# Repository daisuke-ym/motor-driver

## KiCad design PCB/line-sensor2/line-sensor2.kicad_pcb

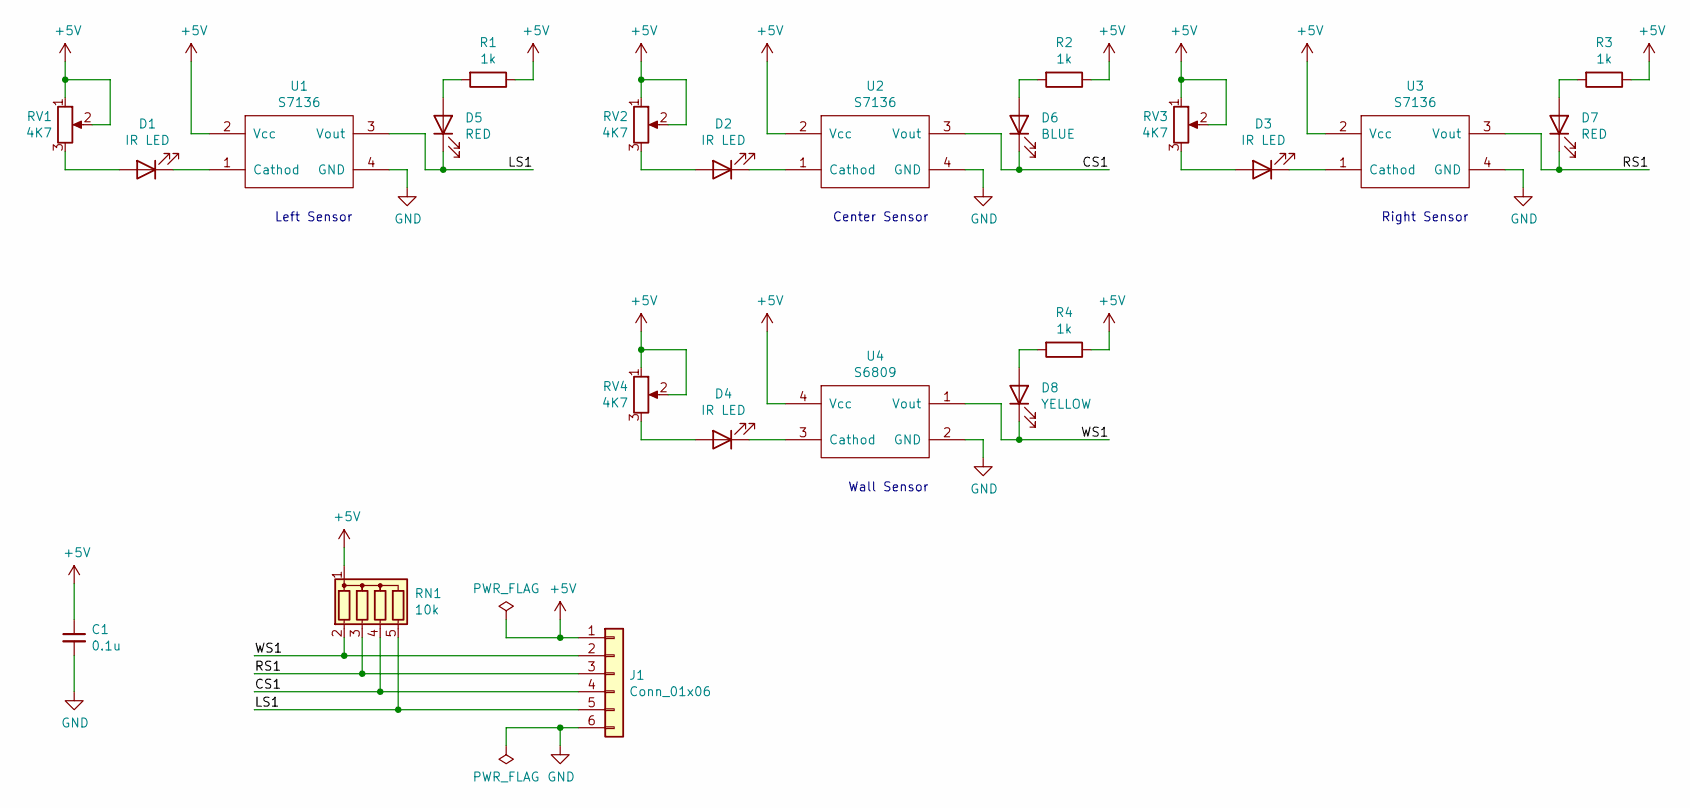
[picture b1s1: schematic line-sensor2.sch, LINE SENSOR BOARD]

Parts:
C1: 0.1u; C_Disc_D3.4mm_W2.1mm_P2.50mm
D1, D2, D3: IR LED; LED_D3.0mm_Clear
D4: IR LED; LED_D3.0mm_Horizontal_O3.81mm_Z6.0mm
D5, D7: RED; LED_D3.0mm_Clear
D6: BLUE; LED_D3.0mm_Clear
D8: YELLOW; LED_D3.0mm_Clear
J1: Conn_01x06; PinHeader_1x06_P2.54mm_Horizontal
R1, R2, R3, R4: 1k; R_Axial_DIN0207_L6.3mm_D2.5mm_P10.16mm_Horizontal
RN1: 10k; R_Array_SIP5
RV1, RV2, RV3, RV4: 4K7; GF063P1
U1, U2, U3: S7136
U4: S6809; S6809_Horizontal_Facedown

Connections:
+5V: C1.1, J1.1, R1.1, R2.1, R3.1, R4.1, RN1.1 (common), RV1.1, RV1.2, RV2.1, RV2.2, RV3.1, RV3.2, RV4.1, RV4.2, U1.2 (Vcc), U2.2 (Vcc), U3.2 (Vcc), U4.4 (Vcc)
/CS1: D6.1 (K), J1.4, RN1.4 (R3), U2.3 (Vout)
/LS1: D5.1 (K), J1.5, RN1.5 (R4), U1.3 (Vout)
/RS1: D7.1 (K), J1.3, RN1.3 (R2), U3.3 (Vout)
/WS1: D8.1 (K), J1.2, RN1.2 (R1), U4.1 (Vout)
GND: C1.2, J1.6, U1.4 (GND), U2.4 (GND), U3.4 (GND), U4.2 (GND)
unnamed: D1.1 (K), U1.1 (Cathod)
unnamed: D1.2 (A), RV1.3
unnamed: D2.1 (K), U2.1 (Cathod)
unnamed: D2.2 (A), RV2.3
unnamed: D3.1 (K), U3.1 (Cathod)
unnamed: D3.2 (A), RV3.3
unnamed: D4.1 (K), U4.3 (Cathod)
unnamed: D4.2 (A), RV4.3
unnamed: D5.2 (A), R1.2
unnamed: D6.2 (A), R2.2
unnamed: D7.2 (A), R3.2
unnamed: D8.2 (A), R4.2

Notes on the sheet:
Wall Sensor
Left Sensor
Center Sensor
Right Sensor

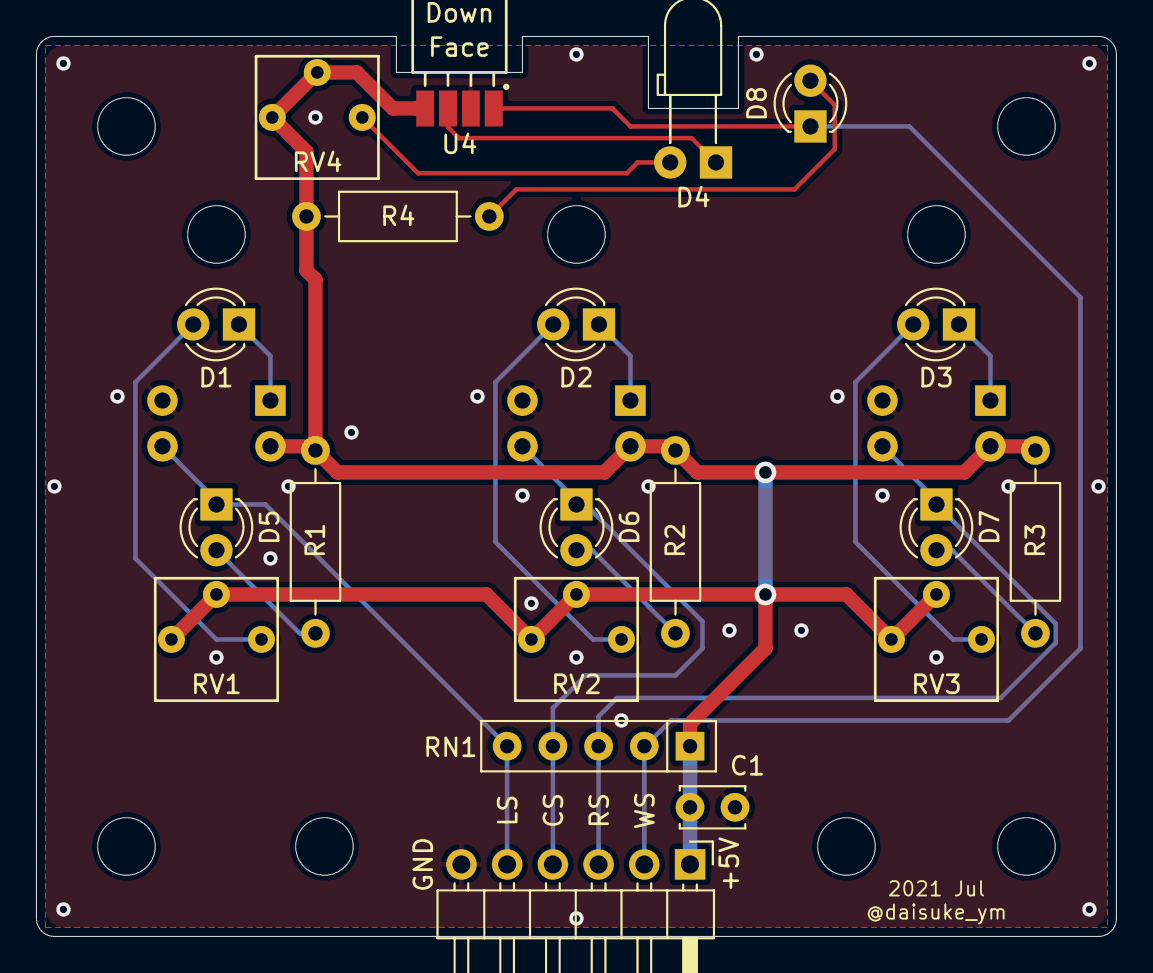
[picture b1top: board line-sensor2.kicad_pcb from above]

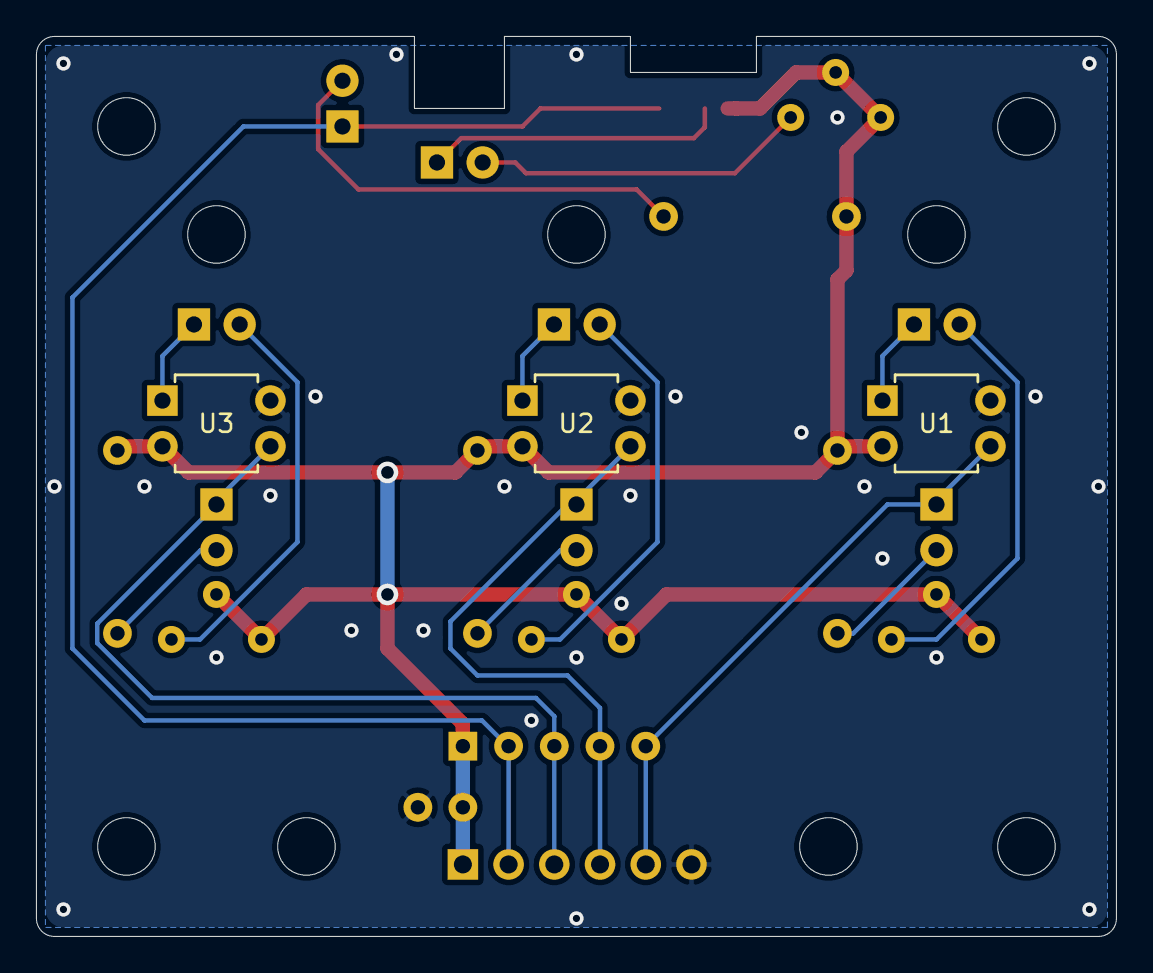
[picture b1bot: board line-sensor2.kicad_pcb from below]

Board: 2 copper layers, 60.0 x 50.0 mm, 32 parts (3 on the bottom side), 18 nets.

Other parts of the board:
MH1, MH2, MH3, MH4, MH5, MH6, MH8, MH9, MH10: MountingHole_3.2mm_M3

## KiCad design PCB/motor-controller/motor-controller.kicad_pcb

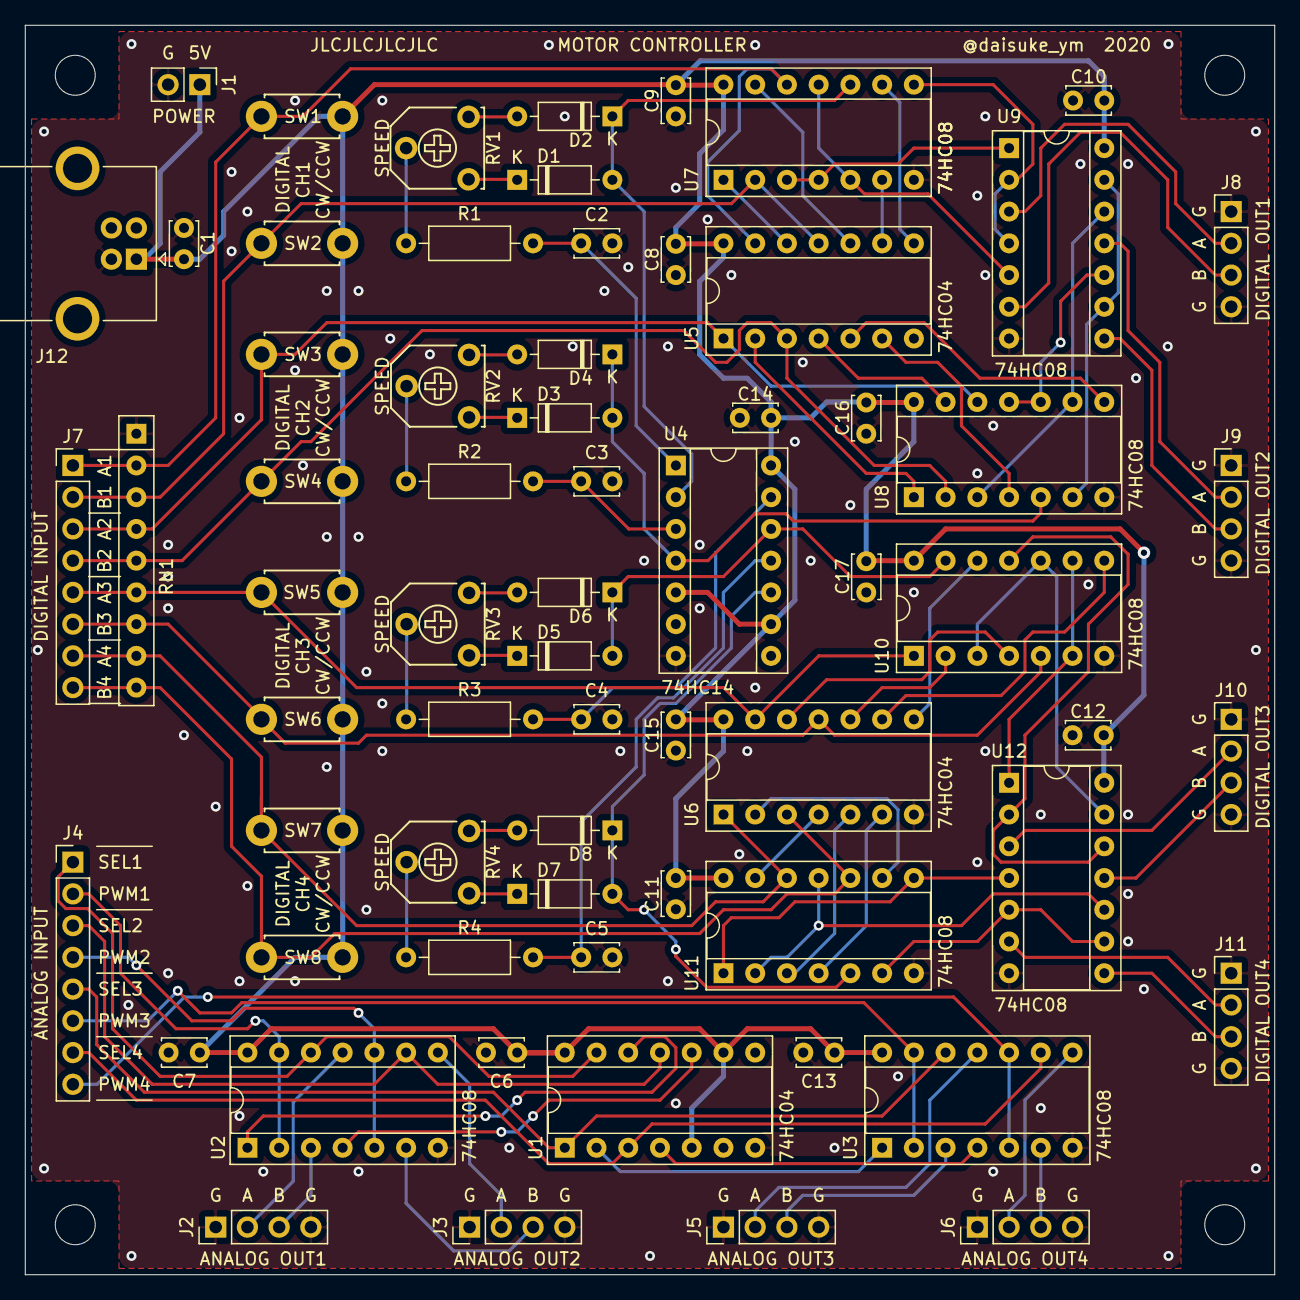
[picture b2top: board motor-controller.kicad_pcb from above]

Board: 2 copper layers, 100.0 x 100.0 mm, 70 parts (0 on the bottom side), 86 nets.

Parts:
C1, C2, C3, C4, C6, C7, C8, C9, C10, C11, C12, C13, C14, C15, C16, C17: 0.1u; C_Disc_D3.4mm_W2.1mm_P2.50mm
C5: C; C_Disc_D3.4mm_W2.1mm_P2.50mm
D1, D2, D3, D4, D5, D6, D7, D8: 1N4148; D_DO-35_SOD27_P7.62mm_Horizontal
J1: POWER; PinHeader_1x02_P2.54mm_Vertical
J2: ANALOG OUT1; PinHeader_1x04_P2.54mm_Vertical
J3: ANALOG OUT2; PinHeader_1x04_P2.54mm_Vertical
J4: ANALOG INPUT; PinHeader_1x08_P2.54mm_Vertical
J5: ANALOG OUT3; PinHeader_1x04_P2.54mm_Vertical
J6: ANALOG OUT4; PinHeader_1x04_P2.54mm_Vertical
J7: DIGITAL INPUT; PinHeader_1x08_P2.54mm_Vertical
J8: DIGITAL OUT1; PinHeader_1x04_P2.54mm_Vertical
J9: DIGITAL OUT2; PinHeader_1x04_P2.54mm_Vertical
J10: DIGITAL OUT3; PinHeader_1x04_P2.54mm_Vertical
J11: DIGITAL OUT4; PinHeader_1x04_P2.54mm_Vertical
J12: USB_B; USB_B_OST_USB-B1HSxx_Horizontal
MH1, MH2, MH3, MH4: MountingHole_3.2mm_M3
R1, R2, R3, R4: R; R_Axial_DIN0207_L6.3mm_D2.5mm_P10.16mm_Horizontal
RN1: 330; R_Array_SIP9
RV1, RV2, RV3, RV4: R_POT; TSR-065
SW1: D1A; TactSW_TVBP06_3.5x6.0-ThroughHole
SW2: D1B; TactSW_TVBP06_3.5x6.0-ThroughHole
SW3: D2A; TactSW_TVBP06_3.5x6.0-ThroughHole
SW4: D2B; TactSW_TVBP06_3.5x6.0-ThroughHole
SW5: D3A; TactSW_TVBP06_3.5x6.0-ThroughHole
SW6: D3B; TactSW_TVBP06_3.5x6.0-ThroughHole
SW7: D4A; TactSW_TVBP06_3.5x6.0-ThroughHole
SW8: D4B; TactSW_TVBP06_3.5x6.0-ThroughHole
U1, U5, U6: 74HC04; DIP-14_W7.62mm_Socket
U2, U3, U7, U8, U9, U10, U11, U12: 74HC08; DIP-14_W7.62mm_Socket
U4: 74HC14; DIP-14_W7.62mm_Socket

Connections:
+5V: C1.1, C6.1, C7.1, C8.1, C9.1, C10.1, C11.1, C12.1, C13.1, C14.1, C15.1, C16.1, C17.1, J1.1, J12.1, SW1.1, SW2.1, SW3.1, SW4.1, SW5.1, SW6.1, SW7.1, SW8.1, U1.5, U1.9, U1.14, U2.14, U3.14, U4.5, U4.9, U4.14, U5.14, U6.14, U7.14, U8.14, U9.14, U10.14, U11.14, U12.14
/AOUT1A: J2.2, U2.11
/AOUT1B: J2.3, U2.3
/AOUT2A: J3.2, U2.8
/AOUT2B: J3.3, U2.6
/AOUT3A: J5.2, U3.11
/AOUT3B: J5.3, U3.3
/AOUT4A: J6.2, U3.8
/AOUT4B: J6.3, U3.6
/DIN1A: J7.1, RN1.2, SW1.2, U5.13, U7.12
/DIN1B: J7.2, RN1.3, SW2.2, U5.11, U7.2
/DIN2A: J7.3, RN1.4, SW3.2, U5.1, U8.12
/DIN2B: J7.4, RN1.5, SW4.2, U5.3, U8.2
/DIN3A: J7.5, RN1.6, SW5.2, U6.13, U10.1
/DIN3B: J7.6, RN1.7, SW6.2, U6.11, U10.5
/DIN4A: J7.7, RN1.8, SW7.2, U6.1, U11.12
/DIN4B: J7.8, RN1.9, SW8.2, U6.3, U11.10
/DOUT1A: J8.2, U9.3
/DOUT1B: J8.3, U9.6
/DOUT2A: J9.2, U9.11
/DOUT2B: J9.3, U9.8
/DOUT3A: J10.2, U12.3
/DOUT3B: J10.3, U12.11
/DOUT4A: J11.2, U12.6
/DOUT4B: J11.3, U12.8
/OSC1: D1.2, D2.1, U4.2, U7.10
/OSC2: D3.2, D4.1, U4.4, U8.5
/OSC3: D5.2, D6.1, U4.12, U10.13
/OSC4: D7.2, D8.1, U4.10, U11.5
/PWM1IN: J4.2, U2.2, U2.13
/PWM2IN: J4.4, U2.5, U2.10
/PWM3IN: J4.6, U3.2, U3.13
/PWM4IN: J4.8, U3.5, U3.10
/SEL1: J4.1, U1.13, U2.12
/SEL2: J4.3, U1.11, U2.9
/SEL3: J4.5, U1.1, U3.12
/SEL4: J4.7, U1.3, U3.9
GND: C1.2, C2.2, C3.2, C4.2, C5.2, C6.2, C7.2, C8.2, C9.2, C10.2, C11.2, C12.2, C13.2, C14.2, C15.2, C16.2, C17.2, J1.2, J2.1, J2.4, J3.1, J3.4, J5.1, J5.4, J6.1, J6.4, J8.1, J8.4, J9.1, J9.4, J10.1, J10.4, J11.1, J11.4, J12.4, RN1.1, U1.7, U2.7, U3.7, U4.7, U5.7, U6.7, U7.7, U8.7, U9.7, U10.7, U11.7, U12.7
unnamed: C2.1, R1.2, U4.1
unnamed: C3.1, R2.2, U4.3
unnamed: C4.1, R3.2, U4.13
unnamed: C5.1, R4.2, U4.11
unnamed: D1.1, RV1.1
unnamed: D2.2, RV1.3
unnamed: D3.1, RV2.1
unnamed: D4.2, RV2.3
unnamed: D5.1, RV3.1
unnamed: D6.2, RV3.3
unnamed: D7.1, RV4.1
unnamed: D8.2, RV4.3
unnamed: R1.1, RV1.2
unnamed: R2.1, RV2.2
unnamed: R3.1, RV3.2
unnamed: R4.1, RV4.2
unnamed: U1.2, U3.1
unnamed: U1.4, U3.4
unnamed: U1.10, U2.4
unnamed: U1.12, U2.1
unnamed: U5.2, U8.1
unnamed: U5.4, U8.13
unnamed: U5.5, U8.8
unnamed: U5.6, U8.4
unnamed: U5.8, U7.9
unnamed: U5.9, U7.6
unnamed: U5.10, U7.13
unnamed: U5.12, U7.1
unnamed: U7.3, U7.4, U9.1
unnamed: U7.8, U9.2, U9.4
unnamed: U7.5, U7.11, U9.5
unnamed: U8.3, U8.9, U9.12
unnamed: U8.6, U9.9, U9.13
unnamed: U8.10, U8.11, U9.10
unnamed: U6.10, U10.2
unnamed: U6.12, U10.4
unnamed: U10.6, U10.9, U12.1
unnamed: U6.9, U10.8
unnamed: U10.3, U10.10, U12.13
unnamed: U10.11, U12.2, U12.12
unnamed: U6.8, U10.12
unnamed: U11.1, U11.8, U12.4
unnamed: U6.5, U11.3
unnamed: U6.6, U11.4
unnamed: U11.6, U12.5, U12.9
unnamed: U6.2, U11.9
unnamed: U11.2, U11.11, U12.10
unnamed: U6.4, U11.13

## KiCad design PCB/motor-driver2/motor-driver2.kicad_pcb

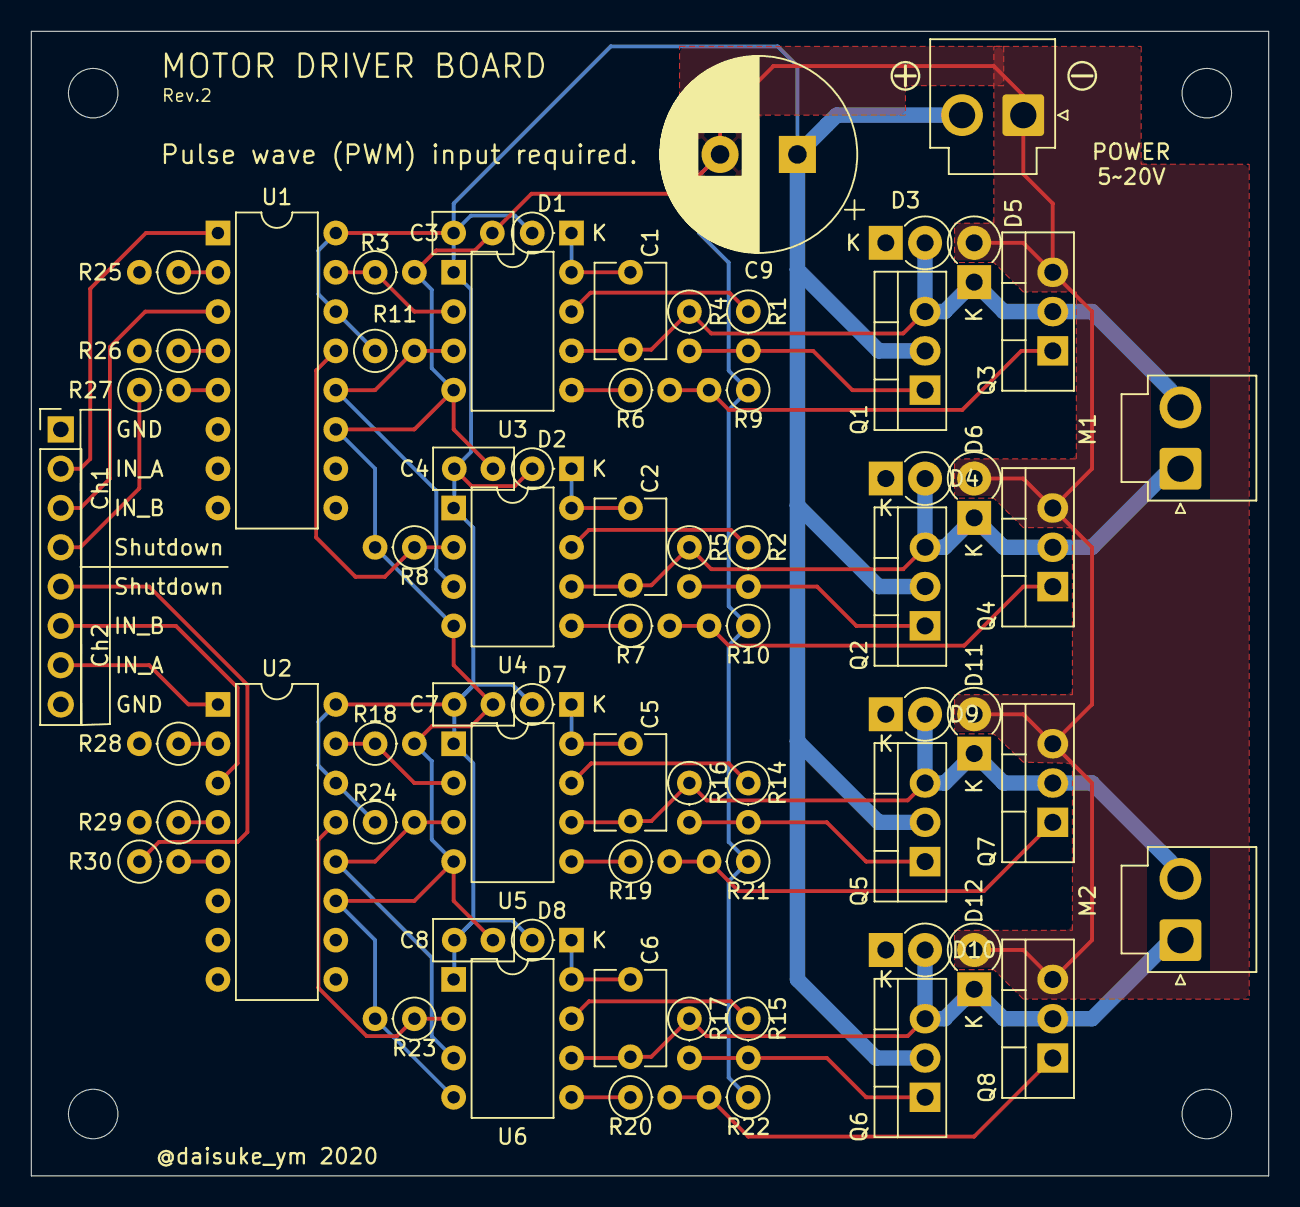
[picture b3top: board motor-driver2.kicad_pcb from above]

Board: 2 copper layers, 80.0 x 74.0 mm, 71 parts (0 on the bottom side), 45 nets.

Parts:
C1, C2, C5, C6: 10u; C_Disc_D6.0mm_W4.4mm_P5.00mm
C3, C4, C7, C8: 0.1u; C_Disc_D5.0mm_W2.5mm_P2.50mm
C9: 470u 50V; CP_Radial_D12.5mm_P5.00mm
D1, D2, D7, D8: 1N4148; D_DO-35_SOD27_P2.54mm_Vertical_KathodeUp
D3, D4, D5, D6, D9, D10, D11, D12: 1N4007; D_DO-41_SOD81_P2.54mm_Vertical_KathodeUp
J1: Motor Power; JST_VH_B2P-VH_1x02_P3.96mm_Vertical
J2: Input Logic; PinHeader_1x08_P2.54mm_Vertical
M1, M2: Motor_DC; JST_VH_B2P-VH_1x02_P3.96mm_Vertical
MH1, MH2, MH3, MH4: MountingHole_3.2mm_M3
Q1, Q2, Q3, Q4, Q5, Q6, Q7, Q8: Q_NMOS_GDS; TO-220-3_Vertical
R1, R2, R4, R5, R6, R7, R9, R10, R14, R15, R16, R17, R19, R20, R21, R22: 47k; R_Axial_DIN0207_L6.3mm_D2.5mm_P2.54mm_Vertical
R3, R8, R11, R18, R23, R24: 10k; R_Axial_DIN0207_L6.3mm_D2.5mm_P2.54mm_Vertical
R25, R26, R27, R28, R29, R30: 390; R_Axial_DIN0207_L6.3mm_D2.5mm_P2.54mm_Vertical
U1, U2: TLP627-4; DIP-16_W7.62mm
U3, U4, U5, U6: IR2302; DIP-8_W7.62mm

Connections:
+BATT: C3.1, C4.1, C7.1, C8.1, C9.1, D1.2, D2.2, D3.1, D4.1, D7.2, D8.2, D9.1, D10.1, J1.2, Q1.2, Q2.2, Q5.2, Q6.2, R11.1, R24.1, U1.14, U1.16, U2.14, U2.16, U3.1, U4.1, U5.1, U6.1
/DR_IN_A1: R3.1, U1.15, U3.2
/DR_IN_A2: R18.1, U2.15, U5.2
/DR_IN_B1: R8.1, U1.13, U4.2
/DR_IN_B2: R23.1, U2.13, U6.2
/DR_SD1: R11.2, U1.12, U3.3, U4.3
/DR_SD2: R24.2, U2.12, U5.3, U6.3
/IN_A1: J2.2, U1.1
/IN_A2: J2.7, U2.1
/IN_B1: J2.3, U1.3
/IN_B2: J2.6, U2.3
/IN_SD1: J2.4, R27.1
/IN_SD2: J2.5, R30.1
GND: J2.1, J2.8, R25.2, R26.2, R28.2, R29.2, U1.6, U2.6
GNDPWR: C3.2, C4.2, C7.2, C8.2, C9.2, D5.2, D6.2, D11.2, D12.2, J1.1, Q3.3, Q4.3, Q7.3, Q8.3, R3.2, R8.2, R9.1, R10.1, R18.2, R21.1, R22.1, R23.2, U1.11, U2.11, U3.4, U4.4, U5.4, U6.4
unnamed: C1.1, D1.1, U3.8
unnamed: C1.2, D3.2, D5.1, M1.2, Q1.3, Q3.2, R4.1, U3.6
unnamed: C2.1, D2.1, U4.8
unnamed: C2.2, D4.2, D6.1, M1.1, Q2.3, Q4.2, R5.1, U4.6
unnamed: C5.1, D7.1, U5.8
unnamed: C5.2, D9.2, D11.1, M2.2, Q5.3, Q7.2, R16.1, U5.6
unnamed: C6.1, D8.1, U6.8
unnamed: C6.2, D10.2, D12.1, M2.1, Q6.3, Q8.2, R17.1, U6.6
unnamed: Q1.1, R1.2, R4.2
unnamed: Q2.1, R2.2, R5.2
unnamed: Q3.1, R6.2, R9.2
unnamed: Q4.1, R7.2, R10.2
unnamed: Q5.1, R14.2, R16.2
unnamed: Q6.1, R15.2, R17.2
unnamed: Q7.1, R19.2, R21.2
unnamed: Q8.1, R20.2, R22.2
unnamed: R1.1, U3.7
unnamed: R2.1, U4.7
unnamed: R6.1, U3.5
unnamed: R7.1, U4.5
unnamed: R14.1, U5.7
unnamed: R15.1, U6.7
unnamed: R19.1, U5.5
unnamed: R20.1, U6.5
unnamed: R25.1, U1.2
unnamed: R26.1, U1.4
unnamed: R27.2, U1.5
unnamed: R28.1, U2.2
unnamed: R29.1, U2.4
unnamed: R30.2, U2.5

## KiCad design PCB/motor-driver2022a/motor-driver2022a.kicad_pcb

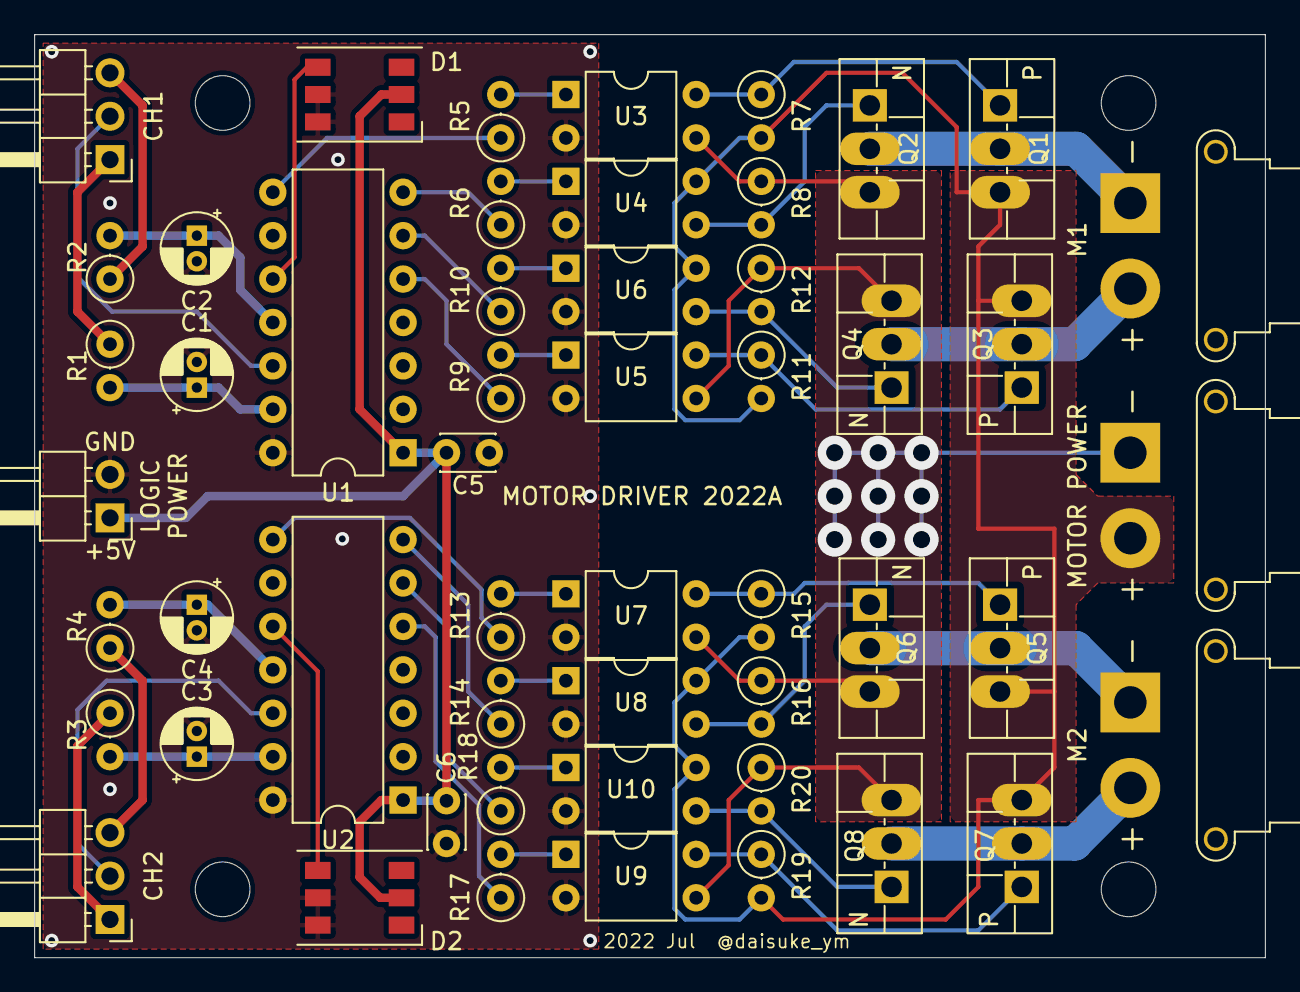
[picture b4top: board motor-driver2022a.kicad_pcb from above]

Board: 2 copper layers, 72.0 x 54.0 mm, 52 parts (0 on the bottom side), 44 nets.

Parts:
C1, C2, C3, C4: 10u; CP_Radial_D4.0mm_P1.50mm
C5, C6: 0.1u; C_Disc_D3.0mm_W2.0mm_P2.50mm
D1, D2: WS2813; LED_WS2812_PLCC6_5.0x5.0mm_P1.6mm
J1: Motor Power; AMASS_XT30PW-F_1x02_P2.50mm_Horizontal
J2: Logic Power; PinHeader_1x02_P2.54mm_Horizontal
J3: Ch1 Input; PinHeader_1x03_P2.54mm_Horizontal
J4: Ch2 Input; PinHeader_1x03_P2.54mm_Horizontal
M1, M2: Motor_DC; AMASS_XT30PW-F_1x02_P2.50mm_Horizontal
Q1, Q3, Q5, Q7: Q_PMOS_GDS; TO-220F-3_Vertical
Q2, Q4, Q6, Q8: Q_NMOS_GDS; TO-220F-3_Vertical
R1, R2, R3, R4: 4k7; R_Axial_DIN0207_L6.3mm_D2.5mm_P2.54mm_Vertical
R5, R6, R9, R10, R13, R14, R17, R18: 330; R_Axial_DIN0207_L6.3mm_D2.5mm_P2.54mm_Vertical
R7, R8, R11, R12, R15, R16, R19, R20: 2k2; R_Axial_DIN0207_L6.3mm_D2.5mm_P2.54mm_Vertical
U1, U2: ATtiny84-20PU; DIP-14_W7.62mm
U3, U4, U5, U6, U7, U8, U9, U10: TLP785; DIP-4_W7.62mm

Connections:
+5V: C5.1, C6.1, D1.2, D2.2, J2.1, U1.1, U2.1
+BATT: J1.2, Q1.3, Q3.3, Q5.3, Q7.3, R7.2, R11.2, R15.2, R19.2, U4.4, U6.4, U8.4, U10.4
/IN1A: J3.1, R1.1
/IN1AA: C1.1, R1.2, U1.13
/IN1B: J3.3, R2.1
/IN1BA: C2.1, R2.2, U1.11
/IN1M: J3.2, U1.12
/IN2A: J4.1, R3.1
/IN2AA: C3.1, R3.2, U2.13
/IN2B: J4.3, R4.1
/IN2BA: C4.1, R4.2, U2.11
/IN2M: J4.2, U2.12
/LED1: D1.4, U1.10
/LED2: D2.4, U2.10
/PC1A: R9.1, U1.5
/PC1B: R10.1, U1.6
/PC1C: R6.1, U1.7
/PC1D: R5.1, U1.8
/PC2A: R17.1, U2.5
/PC2B: R18.1, U2.6
/PC2C: R14.1, U2.7
/PC2D: R13.1, U2.8
GND: C1.2, C2.2, C3.2, C4.2, C5.2, C6.2, D1.5, D1.6, D2.5, D2.6, J2.2, U1.14, U2.14, U3.2, U4.2, U5.2, U6.2, U7.2, U8.2, U9.2, U10.2
GNDPWR: J1.1, Q2.3, Q4.3, Q6.3, Q8.3, R8.1, R12.1, R16.1, R20.1, U3.3, U5.3, U7.3, U9.3
unnamed: M1.1, Q1.2, Q2.2
unnamed: M1.2, Q3.2, Q4.2
unnamed: M2.1, Q5.2, Q6.2
unnamed: M2.2, Q7.2, Q8.2
unnamed: Q1.1, R7.1, U3.4
unnamed: Q2.1, R8.2, U4.3
unnamed: Q3.1, R11.1, U5.4
unnamed: Q4.1, R12.2, U6.3
unnamed: Q5.1, R15.1, U7.4
unnamed: Q6.1, R16.2, U8.3
unnamed: Q7.1, R19.1, U9.4
unnamed: Q8.1, R20.2, U10.3
unnamed: R5.2, U3.1
unnamed: R6.2, U4.1
unnamed: R9.2, U5.1
unnamed: R10.2, U6.1
unnamed: R13.2, U7.1
unnamed: R14.2, U8.1
unnamed: R17.2, U9.1
unnamed: R18.2, U10.1

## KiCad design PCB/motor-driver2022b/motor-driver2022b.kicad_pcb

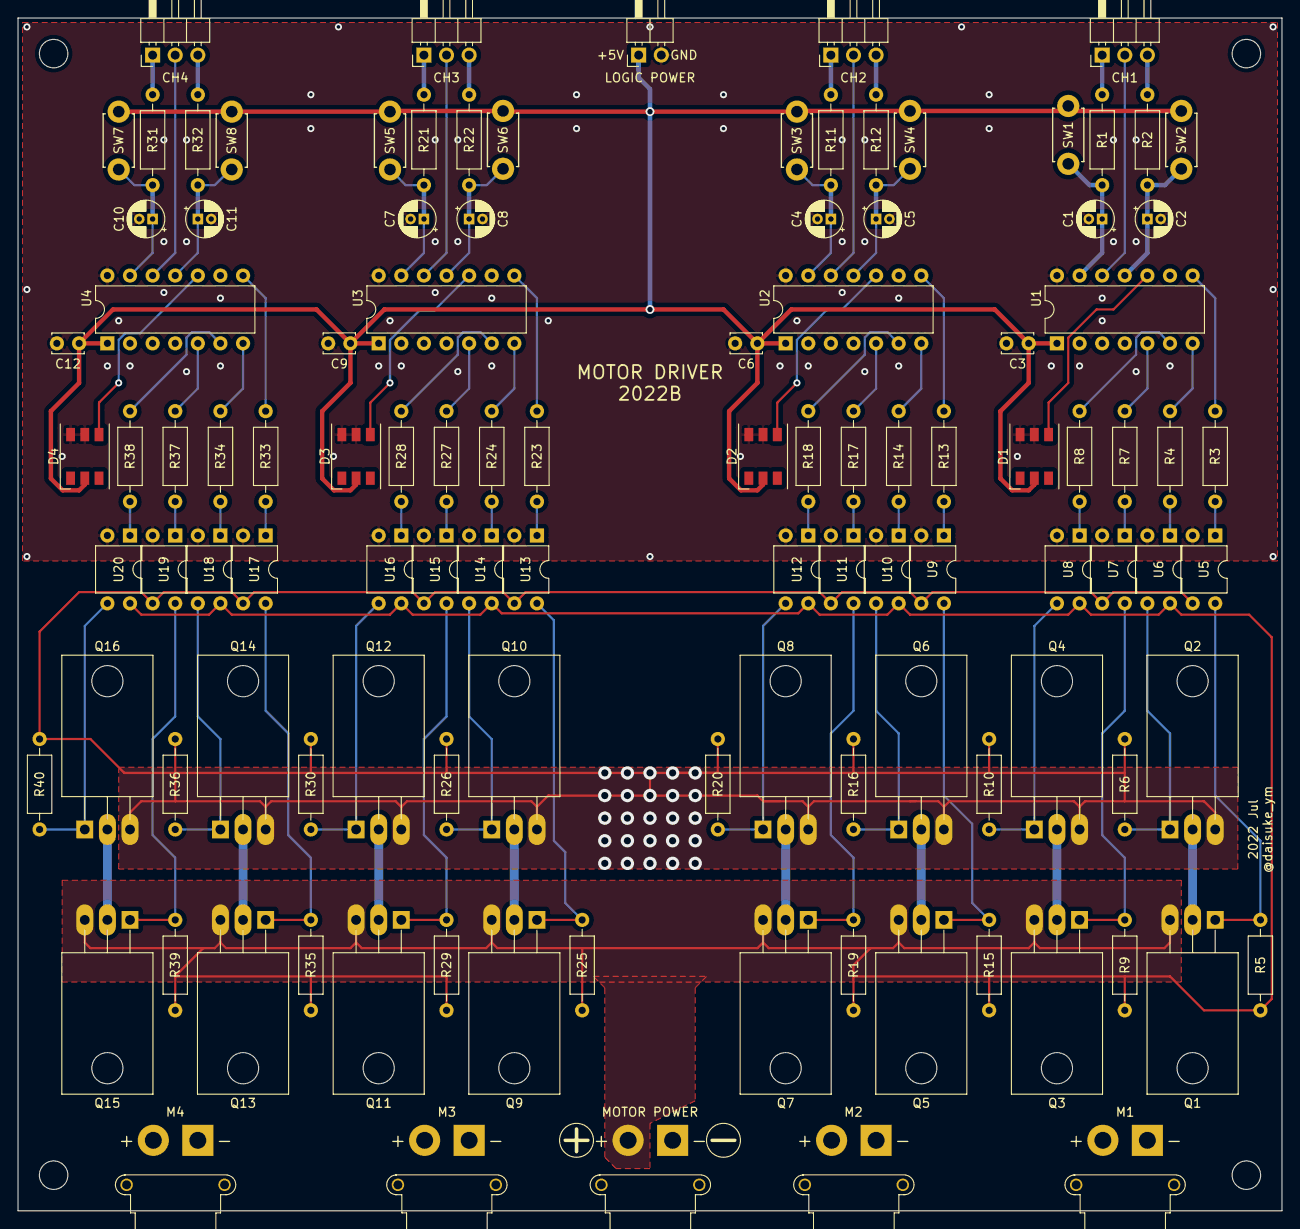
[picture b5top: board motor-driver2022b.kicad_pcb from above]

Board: 2 copper layers, 142.0 x 134.0 mm, 114 parts (0 on the bottom side), 84 nets.

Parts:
C1, C2, C4, C5, C7, C8, C10, C11: 10u; CP_Radial_D4.0mm_P1.50mm
C3, C6, C9, C12: 0.1u; C_Disc_D3.4mm_W2.1mm_P2.50mm
D1, D2, D3, D4: WS2813; LED_WS2812_PLCC6_5.0x5.0mm_P1.6mm
J1: Motor Power; AMASS_XT30PW-F_1x02_P2.50mm_Horizontal
J2: Logic Power; PinHeader_1x02_P2.54mm_Horizontal
J3: Input Ch1; PinHeader_1x03_P2.54mm_Horizontal
J4: Input Ch2; PinHeader_1x03_P2.54mm_Horizontal
J5: Input Ch3; PinHeader_1x03_P2.54mm_Horizontal
J6: Input Ch4; PinHeader_1x03_P2.54mm_Horizontal
M1, M2, M3, M4: Motor_DC; AMASS_XT30PW-F_1x02_P2.50mm_Horizontal
MH1, MH2, MH3, MH4: MountingHole_3.2mm_M3
Q1, Q3, Q5, Q7, Q9, Q11, Q13, Q15: Q_PMOS_GDS; TO-220-3_Horizontal_TabDown
Q2, Q4, Q6, Q8, Q10, Q12, Q14, Q16: Q_NMOS_GDS; TO-220-3_Horizontal_TabDown
R1, R2, R11, R12, R21, R22, R31, R32: 4k7; R_Axial_DIN0207_L6.3mm_D2.5mm_P10.16mm_Horizontal
R3, R4, R7, R8, R13, R14, R17, R18, R23, R24, R27, R28, R33, R34, R37, R38: 330; R_Axial_DIN0207_L6.3mm_D2.5mm_P10.16mm_Horizontal
R5, R6, R9, R10, R15, R16, R19, R20, R25, R26, R29, R30, R35, R36, R39, R40: 2k2; R_Axial_DIN0207_L6.3mm_D2.5mm_P10.16mm_Horizontal
SW1, SW2, SW3, SW4, SW5, SW6, SW7, SW8: SW_Push; TactSW_TVBP06_3.5x6.0-ThroughHole
U1, U2, U3, U4: ATtiny84-20PU; DIP-14_W7.62mm
U5, U6, U7, U8, U9, U10, U11, U12, U13, U14, U15, U16, U17, U18, U19, U20: TLP785; DIP-4_W7.62mm

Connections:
+5V: C3.1, C6.1, C9.1, C12.1, D1.2, D2.2, D3.2, D4.2, J2.1, SW1.2, SW2.2, SW3.2, SW4.2, SW5.2, SW6.2, SW7.2, SW8.2, U1.1, U2.1, U3.1, U4.1
+BATT: J1.2, Q1.3, Q3.3, Q5.3, Q7.3, Q9.3, Q11.3, Q13.3, Q15.3, R5.2, R9.2, R15.2, R19.2, R25.2, R29.2, R35.2, R39.2, U6.4, U8.4, U10.4, U12.4, U14.4, U16.4, U18.4, U20.4
/IN1A: J3.1, R1.1
/IN1AA: C1.1, R1.2, SW1.1, U1.13
/IN1B: J3.3, R2.1
/IN1BA: C2.1, R2.2, SW2.1, U1.11
/IN1M: J3.2, U1.12
/IN2A: J4.1, R11.1
/IN2AA: C4.1, R11.2, SW3.1, U2.13
/IN2B: J4.3, R12.1
/IN2BA: C5.1, R12.2, SW4.1, U2.11
/IN2M: J4.2, U2.12
/IN3A: J5.1, R21.1
/IN3AA: C7.1, R21.2, SW5.1, U3.13
/IN3B: J5.3, R22.1
/IN3BA: C8.1, R22.2, SW6.1, U3.11
/IN3M: J5.2, U3.12
/IN4A: J6.1, R31.1
/IN4AA: C10.1, R31.2, SW7.1, U4.13
/IN4B: J6.3, R32.1
/IN4BA: C11.1, R32.2, SW8.1, U4.11
/IN4M: J6.2, U4.12
/LED1: D1.4, U1.10
/LED2: D2.4, U2.10
/LED3: D3.4, U3.10
/LED4: D4.4, U4.10
/PC1A: R7.1, U1.5
/PC1B: R8.1, U1.6
/PC1C: R4.1, U1.7
/PC1D: R3.1, U1.8
/PC2A: R17.1, U2.5
/PC2B: R18.1, U2.6
/PC2C: R14.1, U2.7
/PC2D: R13.1, U2.8
/PC3A: R27.1, U3.5
/PC3B: R28.1, U3.6
/PC3C: R24.1, U3.7
/PC3D: R23.1, U3.8
/PC4A: R37.1, U4.5
/PC4B: R38.1, U4.6
/PC4C: R34.1, U4.7
/PC4D: R33.1, U4.8
GND: C1.2, C2.2, C3.2, C4.2, C5.2, C6.2, C7.2, C8.2, C9.2, C10.2, C11.2, C12.2, D1.5, D1.6, D2.5, D2.6, D3.5, D3.6, D4.5, D4.6, J2.2, U1.14, U2.14, U3.14, U4.14, U5.2, U6.2, U7.2, U8.2, U9.2, U10.2, U11.2, U12.2, U13.2, U14.2, U15.2, U16.2, U17.2, U18.2, U19.2, U20.2
GNDPWR: J1.1, Q2.3, Q4.3, Q6.3, Q8.3, Q10.3, Q12.3, Q14.3, Q16.3, R6.1, R10.1, R16.1, R20.1, R26.1, R30.1, R36.1, R40.1, U5.3, U7.3, U9.3, U11.3, U13.3, U15.3, U17.3, U19.3
unnamed: M1.1, Q1.2, Q2.2
unnamed: M1.2, Q3.2, Q4.2
unnamed: M2.1, Q5.2, Q6.2
unnamed: M2.2, Q7.2, Q8.2
unnamed: M3.1, Q9.2, Q10.2
unnamed: M3.2, Q11.2, Q12.2
unnamed: M4.1, Q13.2, Q14.2
unnamed: M4.2, Q15.2, Q16.2
unnamed: Q1.1, R5.1, U5.4
unnamed: Q2.1, R6.2, U6.3
unnamed: Q3.1, R9.1, U7.4
unnamed: Q4.1, R10.2, U8.3
unnamed: Q5.1, R15.1, U9.4
unnamed: Q6.1, R16.2, U10.3
unnamed: Q7.1, R19.1, U11.4
unnamed: Q8.1, R20.2, U12.3
unnamed: Q9.1, R25.1, U13.4
unnamed: Q10.1, R26.2, U14.3
unnamed: Q11.1, R29.1, U15.4
unnamed: Q12.1, R30.2, U16.3
unnamed: Q13.1, R35.1, U17.4
unnamed: Q14.1, R36.2, U18.3
unnamed: Q15.1, R39.1, U19.4
unnamed: Q16.1, R40.2, U20.3
unnamed: R3.2, U5.1
unnamed: R4.2, U6.1
unnamed: R7.2, U7.1
unnamed: R8.2, U8.1
unnamed: R13.2, U9.1
unnamed: R14.2, U10.1
unnamed: R17.2, U11.1
unnamed: R18.2, U12.1
unnamed: R23.2, U13.1
unnamed: R24.2, U14.1
unnamed: R27.2, U15.1
unnamed: R28.2, U16.1
unnamed: R33.2, U17.1
unnamed: R34.2, U18.1
unnamed: R37.2, U19.1
unnamed: R38.2, U20.1
